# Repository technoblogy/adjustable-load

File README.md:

# Adjustable Load
An adjustable load that provides a constant-current load for testing power supplies and batteries.

For more information see: <http://www.technoblogy.com/show?4997>.

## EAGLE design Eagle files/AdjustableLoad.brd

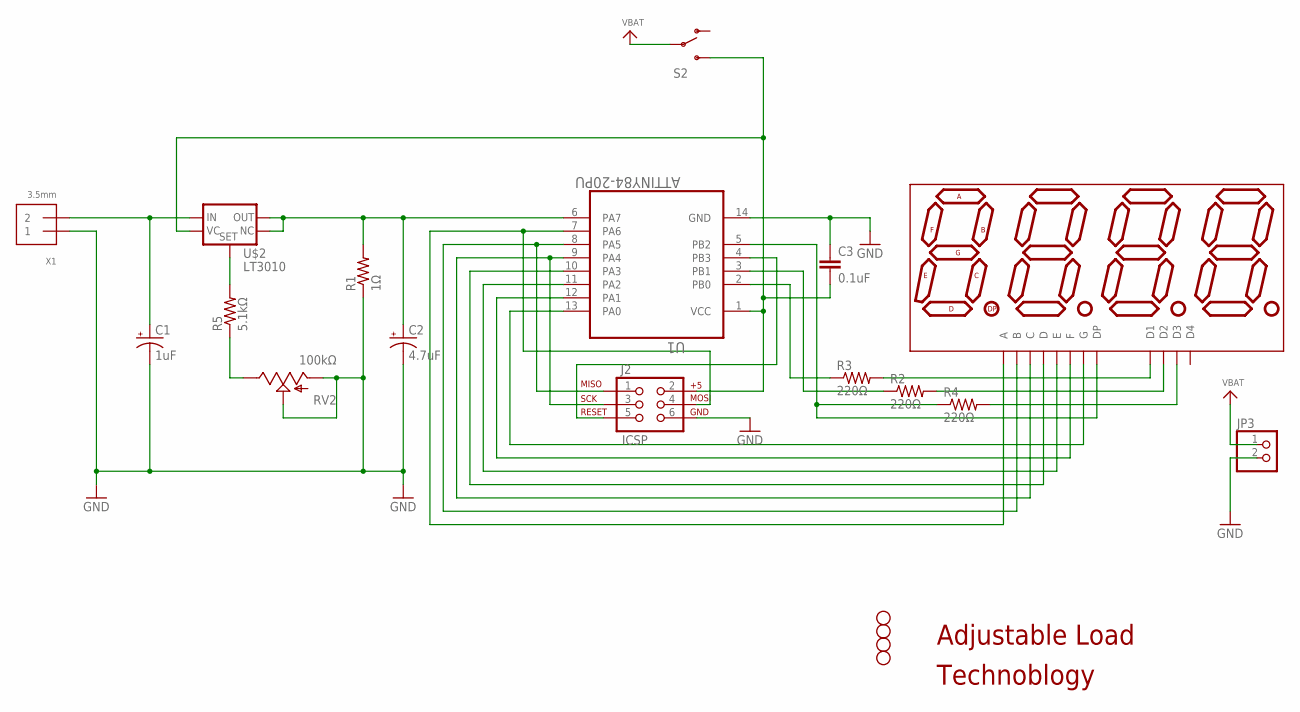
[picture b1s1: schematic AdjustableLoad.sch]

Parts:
C1: 1uF; CPOL-RADIAL-10UF-25V
C2: 4.7uF; CPOL-RADIAL-10UF-25V
C3: 0.1uF; CAP-PTH-SMALL-KIT
DISP1: KYX-2381
J2: ICSP; 2X3
JP1, JP2, JP4, JP5: STAND-OFF
JP3: HEADER-1X2ROUND; 1X02_ROUND
R1: 1Ω; AXIAL-0.6
R2, R3, R4: 220Ω; AXIAL-0.4
R5: 5.1kΩ; AXIAL-0.4
RV2: 100kΩ; ALPS_POT
S2: SWITCH-SPDTPTH; SWITCH-SPDT
U1: ATTINY84-20PU; DIP254P762X533-14
U$2: LT3010; 78XXL
X1: 3.5mm; TERMBLOCK_1X2-3.5MM

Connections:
GND: C1.2 (-), C2.2 (-), C3.1, J2.6, JP3.2, R1.P$1 (1), RV2.P$2 (S), RV2.P$3 (A), U1.14 (GND), X1.1
unnamed: DISP1.5 (G), U1.13 (PA0)
unnamed: R5.P$1 (1), RV2.P$1 (E)
unnamed: J2.5, U1.4 (PB3)
unnamed: C2.1 (+), R1.P$2 (2), U1.6 (PA7), U$2.NC, U$2.OUT
unnamed: R5.P$2 (2), U$2.SET
unnamed: DISP1.10 (F), U1.12 (PA1)
unnamed: DISP1.1 (E), U1.11 (PA2)
unnamed: DISP1.2 (D), U1.10 (PA3)
unnamed: DISP1.4 (C), J2.3, U1.9 (PA4)
unnamed: DISP1.7 (B), J2.1, U1.8 (PA5)
unnamed: DISP1.12 (D1), R3.P$2 (2)
unnamed: DISP1.9 (D2), R2.P$2 (2)
unnamed: DISP1.8 (D3), R4.P$2 (2)
unnamed: R3.P$1 (1), U1.2 (PB0)
unnamed: R2.P$1 (1), U1.3 (PB1)
unnamed: DISP1.3 (DP), R4.P$1 (1), U1.5 (PB2)
unnamed: C1.1 (+), U$2.IN, X1.2
unnamed: DISP1.11 (A), J2.4, U1.7 (PA6)
VBAT: JP3.1, S2.2
VCC: C3.2, J2.2, S2.3 (S), U1.1 (VCC), U$2.VCONTROL

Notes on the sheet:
Adjustable Load
Technoblogy

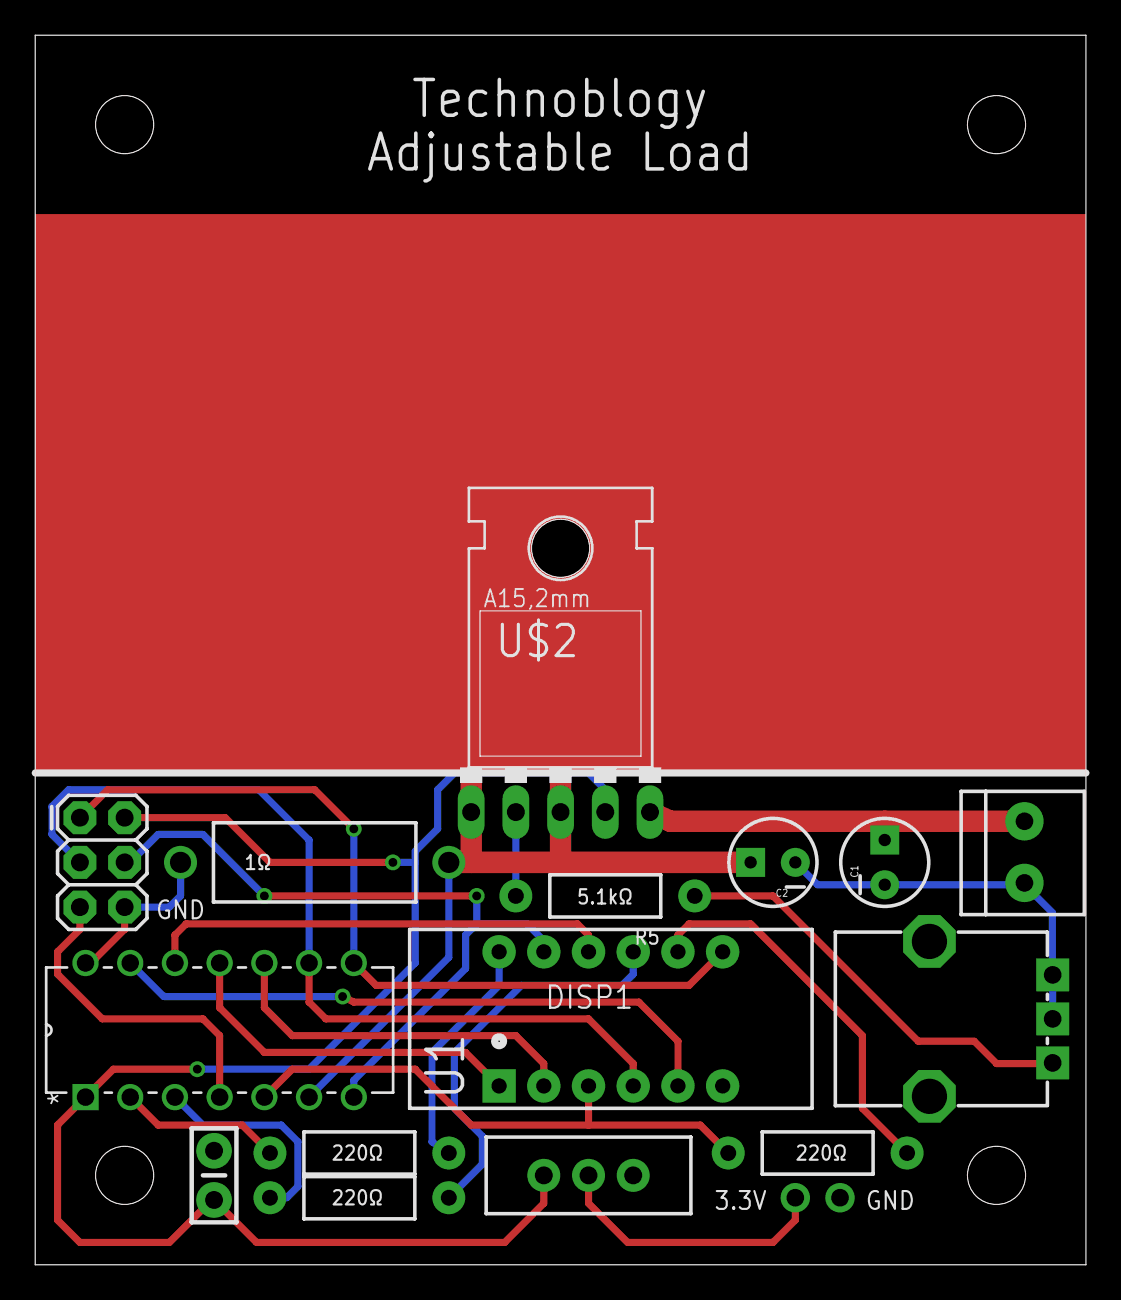
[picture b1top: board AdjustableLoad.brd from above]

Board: 2 copper layers, 59.7 x 69.8 mm, 20 parts (0 on the bottom side), 21 nets.

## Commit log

2023-03-24 Version 1 - 24th March 2023

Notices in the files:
parts and their libraries:
SparkFun-Capacitors: Licensing: Creative Commons ShareAlike 4.0 International - https://creativecommons.org/licenses/by-sa/4.0
microbuilder: This work is placed in the public domain, and may be freely used for commercial and non-commercial work with the following conditions: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
